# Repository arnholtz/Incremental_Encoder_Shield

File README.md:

In this project to reduce the bounce /communication noice/ the single channel Shmitt-trigger input logic inverter /in sot-23-5 package/ are used

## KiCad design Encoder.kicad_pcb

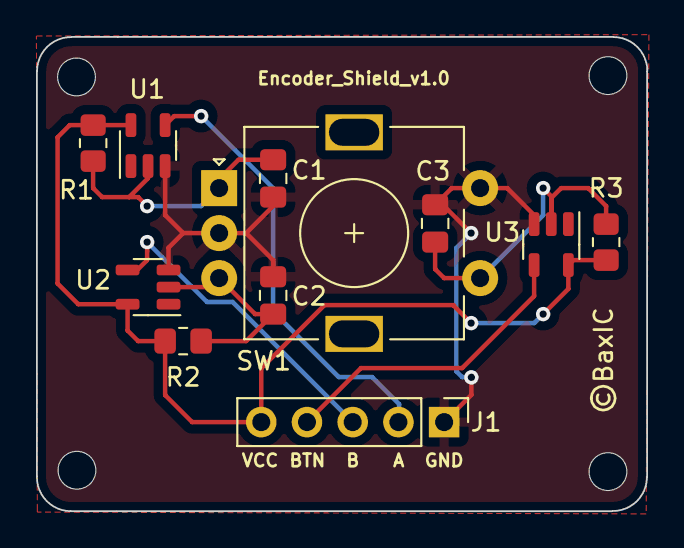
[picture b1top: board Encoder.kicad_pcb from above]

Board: 2 copper layers, 33.9 x 26.4 mm, 11 parts (0 on the bottom side), 8 nets.

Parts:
C1, C2, C3: C; C_0805_2012Metric_Pad1.18x1.45mm_HandSolder
J1: Conn_01x05_Male; PinHeader_1x05_P2.54mm_Vertical
R1, R2, R3: R_US; R_0805_2012Metric_Pad1.20x1.40mm_HandSolder
SW1: RotaryEncoder_Switch; RotaryEncoder_Alps_EC11E-Switch_Vertical_H20mm
U1, U2, U3: SN74LVC1G14DBV; SOT-23-5

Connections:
GND: C1.2, C2.2, C3.2, J1.1, SW1.C, SW1.S2, U1.3 (GND), U2.3 (GND), U3.3 (GND)
unnamed: C1.1, R1.2, SW1.A, U1.2
unnamed: C2.1, R2.2, SW1.B, U2.2
unnamed: C3.1, R3.2, SW1.S1, U3.2
unnamed: J1.2, U1.4
unnamed: J1.3, U2.4
unnamed: J1.4, U3.4
VCC: J1.5, R1.1, R2.1, R3.1, U1.5 (VCC), U2.5 (VCC), U3.5 (VCC)

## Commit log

2022-11-27 1sh commit
2022-11-27 Add the EC-11 encoder library files

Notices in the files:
Encoder.kicad_pcb:
©BaxIC
